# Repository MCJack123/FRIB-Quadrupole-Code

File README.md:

# FRIB-Quadrupole-Code

## ECE480-Distribution.X
MPLAB X project for microcontroller on the distribution board.

### Building
Use [MPLAB X](https://www.microchip.com/en-us/tools-resources/develop/mplab-x-ide) with XC8 to build the project. The built HEX file will be in `dist/default/production/ECE480-Distribution.X.production.hex`.

### Flashing
The board has Microchip ICSP capabilities for programming. Use the following pin assignments to connect to an ICSP programmer:
| ICSP pin | Qw/ST pin |
|----------|-----------|
| Vdd      | 3.3V      |
| Vss      | GND       |
| ICSPDAT  | SDA       |
| ICSPCLK  | SCL       |
| Vpp/MCLR | JP1 (side closer to MCU) |

Note that MCLR connects directly to the JP1 jumper pad, which must not be bridged.

Programming may be done with an official Microchip PICkit or ICD 4 or 5. If you don't have one available, you can use a Raspberry Pi Pico running [this programmer firmware](https://github.com/MCJack123/pico-icsp-programmer). To use, build and upload the program, connect the pins as directed, and simply send the HEX file over the serial connection that appears.

## pico-bar-adjust
Demo program for a frontend with 8 bars, sending 3-bit signals over I2C. Not the final interface.

Requires a Raspberry Pi Pico mounted on a [Pimoroni Pico Display Pack 2.8"](https://shop.pimoroni.com/products/pico-display-pack-2-8). Building requires the Pico SDK, Pico SDK Extras, and Pimoroni Pico libraries.

Use buttons A/B to select the row, and X/Y to adjust the value.

## pico-i2c-driver
Final program to adapt USB serial data to I2C. Use CMake and the Pico SDK to build. Flash the built UF2 using the BOOT button.

## Initial-Distribution-Board
KiCAD PCB files for the first design of the distribution board, before integration with the power splitter and phase shifter. Production files for JLCPCB are included in `production/`.

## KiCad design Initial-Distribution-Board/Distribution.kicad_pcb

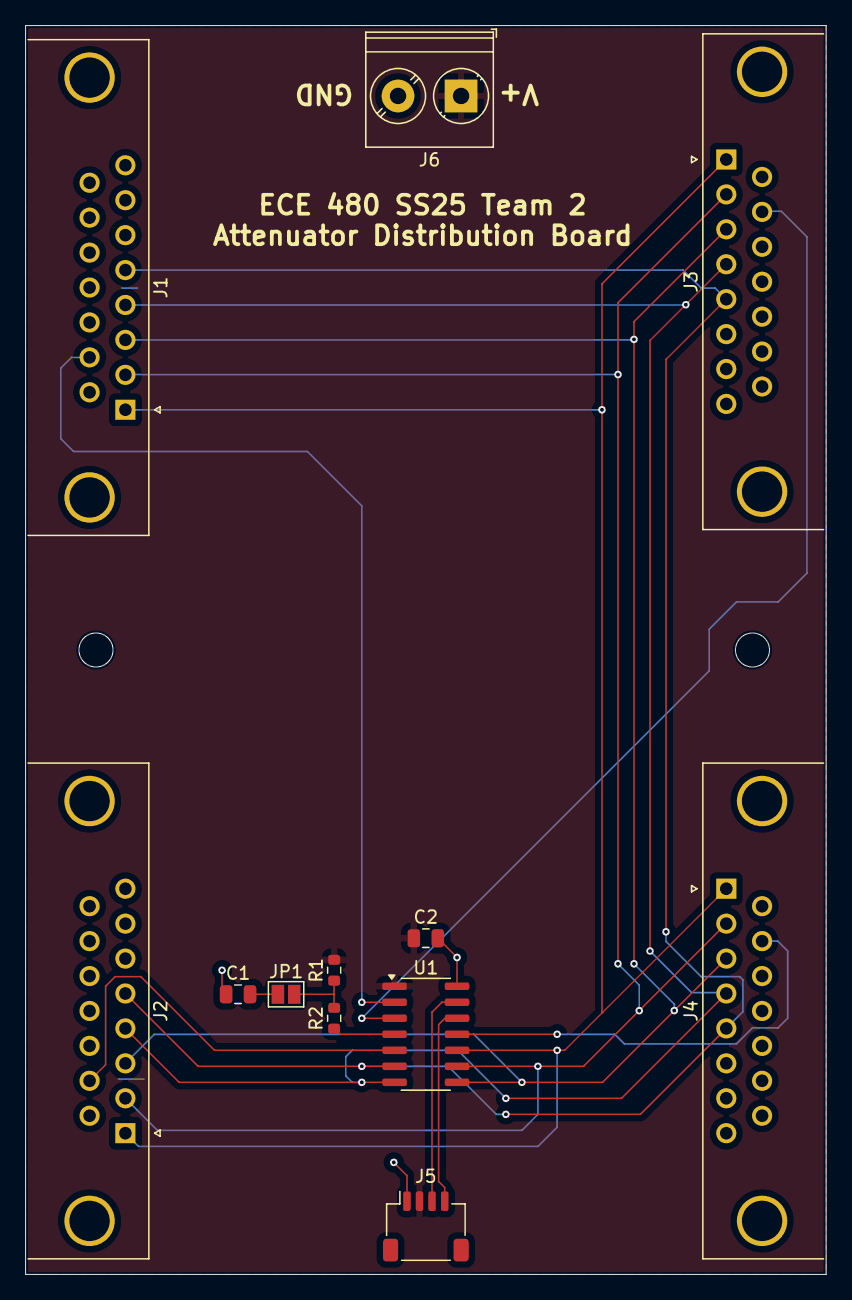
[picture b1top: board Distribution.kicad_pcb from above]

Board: 2 copper layers, 63.5 x 99.1 mm, 14 parts (0 on the bottom side), 16 nets.

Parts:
C1, C2: 0.1µF; C_0805_2012Metric
H1, H1#2: MountingHole_2.7mm_M2.5_ISO7380
J1, J2, J3, J4: DSUB-15_Female_Horizontal_P2.77x2.84mm_EdgePinOff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; DSUB-15_Female_Horizontal_P2.77x2.84mm_EdgePinOffset4.94mm_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
J5: JST_SH_SM04B-SRSS-TB_1x04-1MP_P1.00mm_Horizontal
J6: TerminalBlock_Phoenix_PT-1,5-2-5.0-H_1x02_P5.00mm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; TerminalBlock_Phoenix_PT-1,5-2-5.0-H_1x02_P5.00mm_Horizontal
JP1: SolderJumper-2_P1.3mm_Open_Pad1.0x1.5mm
R1: 10kΩ; R_0603_1608Metric
R2: 470Ω; R_0603_1608Metric
U1: PIC18F04Q40; SOIC-14_3.9x8.7mm_P1.27mm

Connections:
/C0: J1.1, J2.1, J3.1, J4.1, U1.10
/C1: J1.2, J2.2, J3.2, J4.2, U1.9
/C2: J1.3, J2.3, J3.3, J4.3, U1.8
/C3: J1.4, J2.4, J3.4, J4.4, U1.7
/C4: J1.5, J2.5, J3.5, J4.5, U1.6
/L0: J1.10, U1.2
/L1: J2.10, U1.5
/L2: J3.10, U1.3
/L3: J4.10, U1.11
/SCL: J5.4, U1.12
/SDA: J5.3, U1.13
GND: C1.1, C2.2, J1.0, J1.15, J2.0, J2.15, J3.0, J3.15, J4.0, J4.15, J5.1, J6.2, U1.14
MCLR_HOLD: JP1.2, R1.1, R2.2
MCLR_HOLD_CAP: C1.2, JP1.1
VDD: C2.1, J5.2, J6.1, R1.2, U1.1
~MCLR: R2.1, U1.4

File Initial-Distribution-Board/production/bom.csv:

Designator,Footprint,Quantity,Value,LCSC Part #
"C1, C2",0805,2,0.1µF,
"J1, J2, J3, J4",DSUB-15_Female_Horizontal_P2.77x2.84mm_EdgePinOffset4.94mm_Housed_MountingHolesOffset4.94mm,4,DSUB-15_Female_Horizontal_P2.77x2.84mm_EdgePinOffset4.94mm_Housed_MountingHolesOffset4.94mm,
J5,JST_SH_SM04B-SRSS-TB_1x04-1MP_P1.00mm_Horizontal,1,JST_SH_SM04B-SRSS-TB_1x04-1MP_P1.00mm_Horizontal,
J6,"TerminalBlock_Phoenix_PT-1,5-2-5.0-H_1x02_P5.00mm_Horizontal",1,"TerminalBlock_Phoenix_PT-1,5-2-5.0-H_1x02_P5.00mm_Horizontal",
R1,0603,1,10kΩ,
R2,0603,1,470Ω,
U1,SOIC-14_3.9x8.7mm_P1.27mm,1,PIC18F04Q40,

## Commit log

2025-03-19 Uploaded
2025-04-18 Added board design, I2C driver
